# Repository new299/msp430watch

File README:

You can read about the project here: http://41j.com/blog/2011/09/msp430-watch/

This code is probably woefully broken. You need to comment/uncomment code depending on the lcd type (3310 or 3530)

Requires msp430gcc and mspdebug. On Ubuntu 12.04 they can be installed with:

sudo apt-get install mspdebug gcc-msp430

To build:

make msp430watch.elf

To program the code:

make msp430watch.program

Nava Whiteford - new at 41j dot com

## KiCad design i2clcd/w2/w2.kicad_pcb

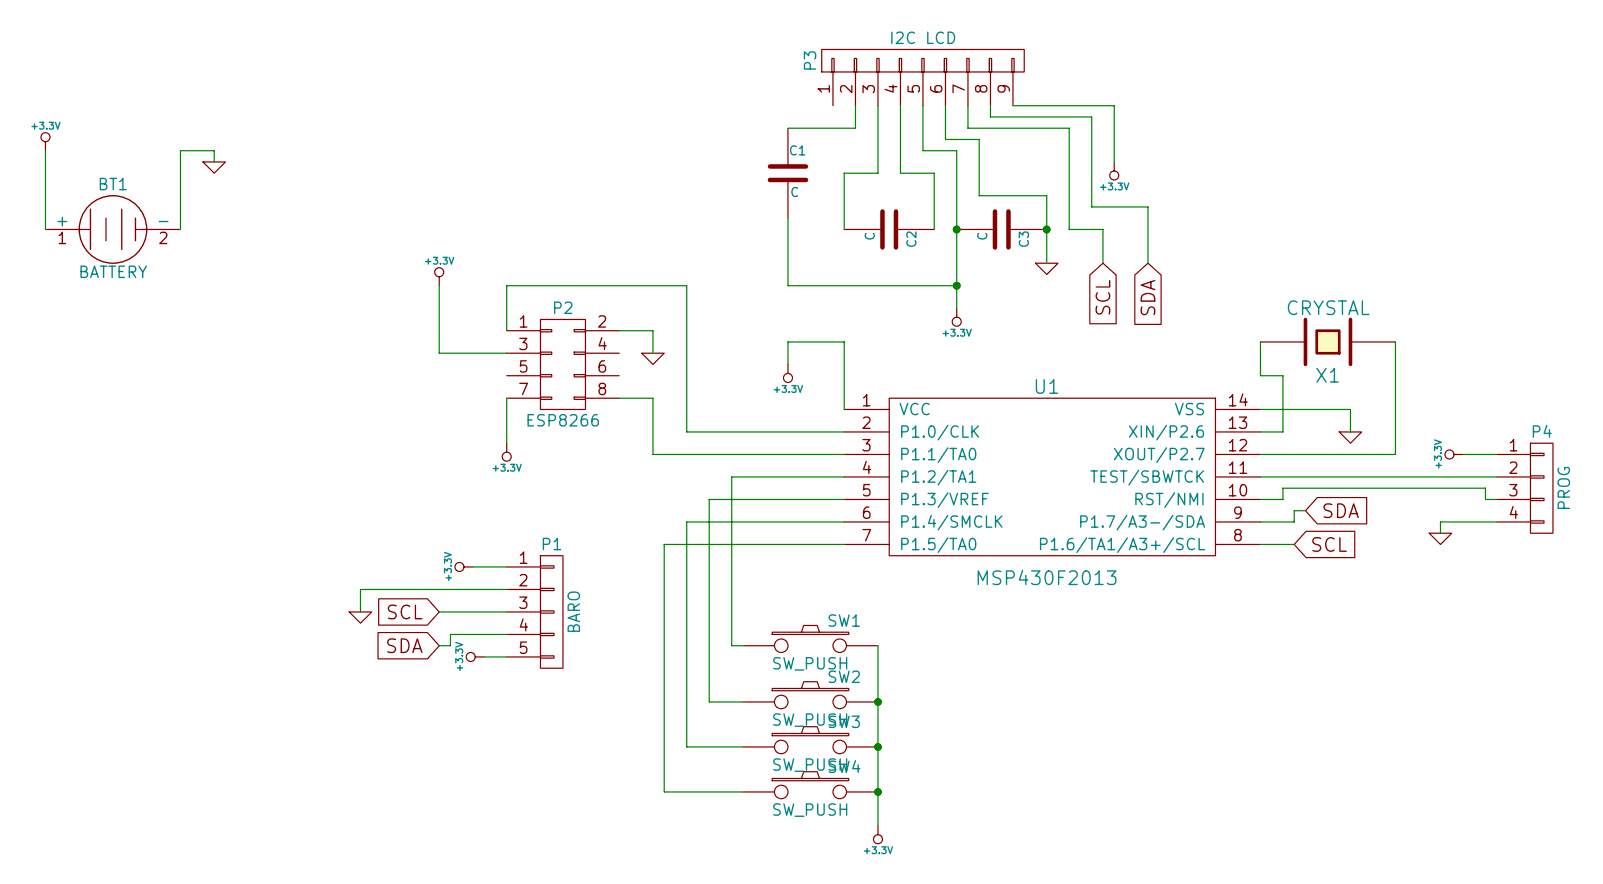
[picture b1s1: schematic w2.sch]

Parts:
BT1: BATTERY; BC2003-CR2032
C1, C2, C3: C; C_0603
P1: BARO; Pin_Header_Straight_1x05
P2: ESP8266; Pin_Header_Straight_2x04
P3: I2C LCD; 01x09_2mm
P4: PROG; Pin_Header_Straight_1x04
SW1, SW2, SW3, SW4: SW_PUSH; SIDE_SW666
U1: MSP430F2013; TSSOP-14
X1: CRYSTAL; Crystal_Round_Horizontal_2mm

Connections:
+3.3V: BT1.1 (+), C1.2, C3.2, P1.1, P1.5, P2.3, P2.7, P3.5, P3.9, P4.1, SW1.2, SW2.2, SW3.2, SW4.2, U1.1 (VCC)
GND: BT1.2 (-), C3.1, P1.2, P2.2, P3.6, P4.4, U1.14 (VSS)
unnamed: C1.1, P3.2
unnamed: C2.1, P3.4
unnamed: C2.2, P3.3
unnamed: P2.1, U1.2 (P1.0/CLK)
unnamed: P2.8, U1.3 (P1.1/TA0)
unnamed: P4.2, U1.11 (TEST/SBWTCK)
unnamed: P4.3, U1.10 (RST/NMI)
unnamed: SW1.1, U1.4 (P1.2/TA1)
unnamed: SW2.1, U1.5 (P1.3/VREF)
unnamed: SW3.1, U1.6 (P1.4/SMCLK)
unnamed: SW4.1, U1.7 (P1.5/TA0)
unnamed: U1.12 (XOUT/P2.7), X1.1
unnamed: U1.13 (XIN/P2.6), X1.2
SCL: P1.3, P3.7, U1.8 (P1.6/TA1/A3+/SCL)
SDA: P1.4, P3.8, U1.9 (P1.7/A3-/SDA)

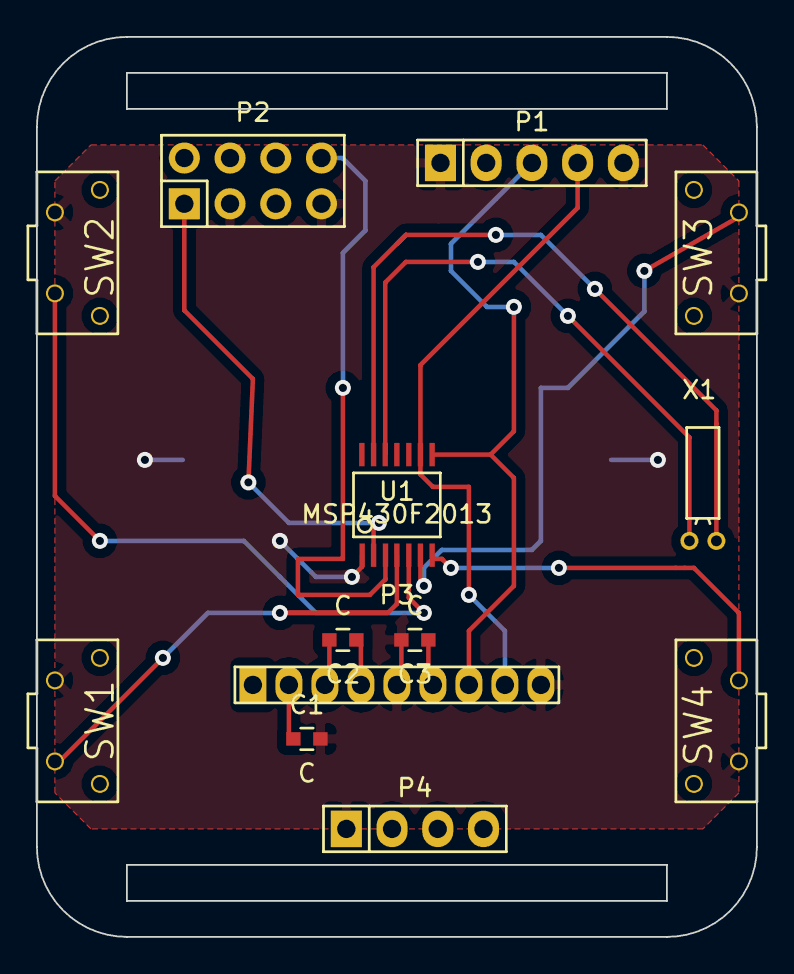
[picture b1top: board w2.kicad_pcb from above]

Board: 2 copper layers, 40.0 x 50.0 mm, 14 parts (1 on the bottom side), 17 nets.

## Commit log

2012-04-18 initial checkin
2012-04-23 added my email address to the README
2012-05-13 updated compiler path (use system install)
2012-05-13 moving things around, tidying up Makefile
2012-05-13 updated readme to note the borkage
2012-05-13 added programming target
2012-05-13 updated Makefile with correct programming options
2012-05-13 breaking lcd code out into own header files. Initial 3310 LCD support.
2012-05-13 some comments, change Makefile all target
2014-11-22 msp430watch i2c code, moving other files
2014-11-22 added back old nokia lcd files
2014-11-26 working! (07.c)
2015-01-22 added new design
